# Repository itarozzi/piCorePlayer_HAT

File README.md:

# piCorePlayer RaspberryPi 3 HAT

A Raspberry Pi 3 HAT for my piCorePlayer device.

By Ivan Tarozzi
- itarozzi@gmail.com
- ivan.tarozzi@fablabromagna.org

> CAUTION!!!! Dont't use yet. The circuit is under test and the schema and PCB are probabily wrong due a wrong relay connection. I'll update the circuit as soon as possible

## Description
When I decided to use a RaspberryPi and the [piCorePlayer project](https://www.picoreplayer.org/) to stream my music library from NAS to HiFi I encountered the problem to have a proper PSU for the RaspberryPi, having the ability to shutdown the system in safe mode and using a HW button for a real ON/OFF.

This becasuse the RaspberryPi 3 lacks of a native way to halt and restart by buttons.

I found a solution in a forum (see credits) and I decided to create a prototype using handwired assembly.

But in the same days FablabRomagna (the FabLab where I play as maker here in Rimini-IT) organized a course about KiCad so I decided to give it a try. And here the result of my attempt to use KiCad for creating my HAT.

Instead of use dupont wires on the RaspberryPi 40-pin connector I created a HAT to connect the power module and at the same time use it for the DAC, the TFT display, the encoder and buttons for the front panel (piCorePlayer commands).

I used a lot of components I already owned, so I adapted the circuit to that things.

I creatd the PCB and using STEP file generated  by KiCad as reference, I created a case with FreeCAD.

## How it works

The power section use a latched relay to power the RaspberryPi throught the 40-pin GPIO connector, when a button is pressed. I changed the original circuit to use the same button to also poweroff the device.

So, in its initial state, the START/STOP button (replicated in PCB and front panel) drive the transistor Q1 to switch-on the relay and power on the RaspberryPi.

When the RaspberryPi is on and the START/STOP button  is pressed again, a high level is sent to GPIO_16 pin. A little daemon intercept this event and execute the safe power-off using linux commands.

When the RaspberryPi is halted, the GPIO_26 rise (using poweroff overlay) and this reset the relay via the Q2 transistor.
And additional safe button is used to activate Q2 if the software poweroff fails (hope ever used).

> there is a hypothetical race condition when the START/STOP button is pressed the first time, because when the relay switch its state, it rise the level on GPIO_16. But in real case, the Raspberry is booting so the shutdown daemon is not running until 10/12 seconds. I think it will works in this first version

## TODO

- may be a smd version
- DAC integration in the HAT

## License

- Hardware design is released under CERN-OHL-S v2 license
- Software is released under GPL3 License
- Documentation is released under CC BY-SA 3.0

## Credits

- [piCorePlayer project](https://www.picoreplayer.org/)
- [Seamus](https://raspberrypi.stackexchange.com/questions/142837/questions-on-dtoverlay-gpio-poweroff) for the power circuit
- [Maurizio Conti @ FablabRomagna](https://github.com/mconti) for forced me to try KiCad :)

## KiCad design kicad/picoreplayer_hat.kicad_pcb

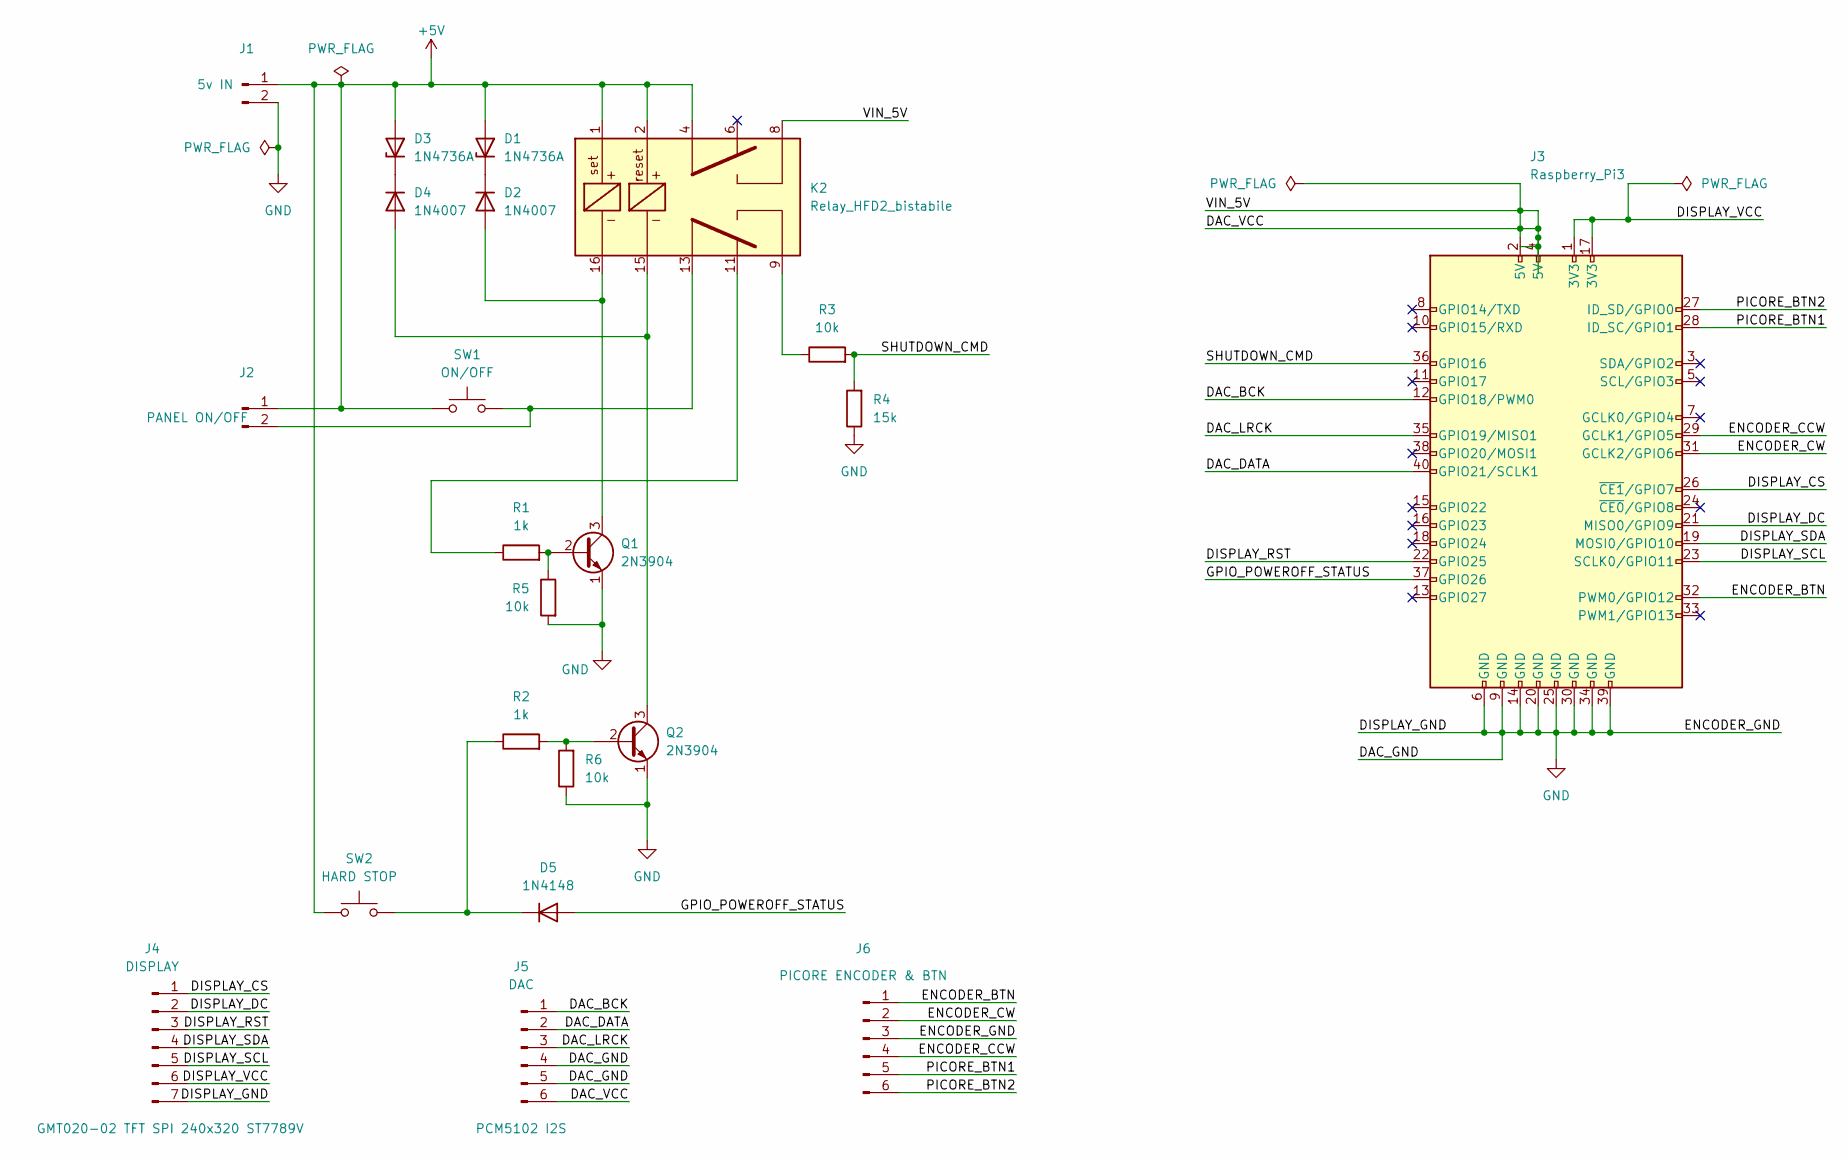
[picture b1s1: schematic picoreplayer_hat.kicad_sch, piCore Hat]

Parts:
D1, D3: 1N4736A; D_DO-41_SOD81_P7.62mm_Horizontal
D2, D4: 1N4007; D_DO-41_SOD81_P10.16mm_Horizontal
D5: 1N4148; D_DO-35_SOD27_P7.62mm_Horizontal
J1: 5v IN; JST_EH_B2B-EH-A_1x02_P2.50mm_Vertical
J2: PANEL ON/OFF; PinHeader_1x02_P2.54mm_Horizontal
J3: Raspberry_Pi3; PinSocket_2x20_P2.54mm_Vertical
J4: DISPLAY; PinHeader_1x07_P2.54mm_Horizontal
J5: DAC; PinHeader_1x06_P2.54mm_Horizontal
J6: PICORE ENCODER & BTN; PinHeader_1x06_P2.54mm_Horizontal
K2: Relay_HFD2_bistabile; Relay_HFD2-05ML2A_2 coils latching
Q1, Q2: 2N3904; TO-92_Inline
R1, R2: 1k; R_Axial_DIN0207_L6.3mm_D2.5mm_P7.62mm_Horizontal
R3, R5, R6: 10k; R_Axial_DIN0207_L6.3mm_D2.5mm_P7.62mm_Horizontal
R4: 15k; R_Axial_DIN0207_L6.3mm_D2.5mm_P7.62mm_Horizontal
SW1: ON/OFF; SW_PUSH_6mm_H4.3mm
SW2: HARD STOP; SW_PUSH_6mm_H4.3mm

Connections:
+5V: D1.2 (A), D3.2 (A), J1.1, J2.1, K2.1, K2.2, K2.4, SW1.1, SW2.1
/DAC_BCK: J3.12 (GPIO18/PWM0), J5.1
/DAC_DATA: J3.40 (GPIO21/SCLK1), J5.2
/DAC_LRCK: J3.35 (GPIO19/MISO1), J5.3
/DAC_VCC: J3.2 (5V), J3.4 (5V), J5.6, K2.8
/DISPLAY_CS: J3.26 (~CE1/GPIO7), J4.1
/DISPLAY_DC: J3.21 (MISO0/GPIO9), J4.2
/DISPLAY_RST: J3.22 (GPIO25), J4.3
/DISPLAY_SCL: J3.23 (SCLK0/GPIO11), J4.5
/DISPLAY_SDA: J3.19 (MOSI0/GPIO10), J4.4
/DISPLAY_VCC: J3.1 (3V3), J3.17 (3V3), J4.6
/ENCODER_BTN: J3.32 (PWM0/GPIO12), J6.1
/ENCODER_CCW: J3.29 (GCLK1/GPIO5), J6.4
/ENCODER_CW: J3.31 (GCLK2/GPIO6), J6.2
/GPIO_POWEROFF_STATUS: D5.2 (A), J3.37 (GPIO26)
/PICORE_BTN1: J3.28 (ID_SC/GPIO1), J6.5
/PICORE_BTN2: J3.27 (ID_SD/GPIO0), J6.6
/SHUTDOWN_CMD: J3.36 (GPIO16), R3.2, R4.2
GND: J1.2, J3.6 (GND), J3.9 (GND), J3.14 (GND), J3.20 (GND), J3.25 (GND), J3.30 (GND), J3.34 (GND), J3.39 (GND), J4.7, J5.4, J5.5, J6.3, Q1.1 (E), Q2.1 (E), R4.1, R5.2, R6.1
unnamed: D1.1 (K), D2.1 (K)
unnamed: D2.2 (A), K2.16, Q1.3 (C)
unnamed: D3.1 (K), D4.1 (K)
unnamed: D4.2 (A), K2.15, Q2.3 (C)
unnamed: D5.1 (K), R2.1, SW2.2
unnamed: J2.2, K2.13, SW1.2
unnamed: K2.9, R3.1
unnamed: K2.11, R1.1
unnamed: Q1.2 (B), R1.2, R5.1
unnamed: Q2.2 (B), R2.2, R6.2

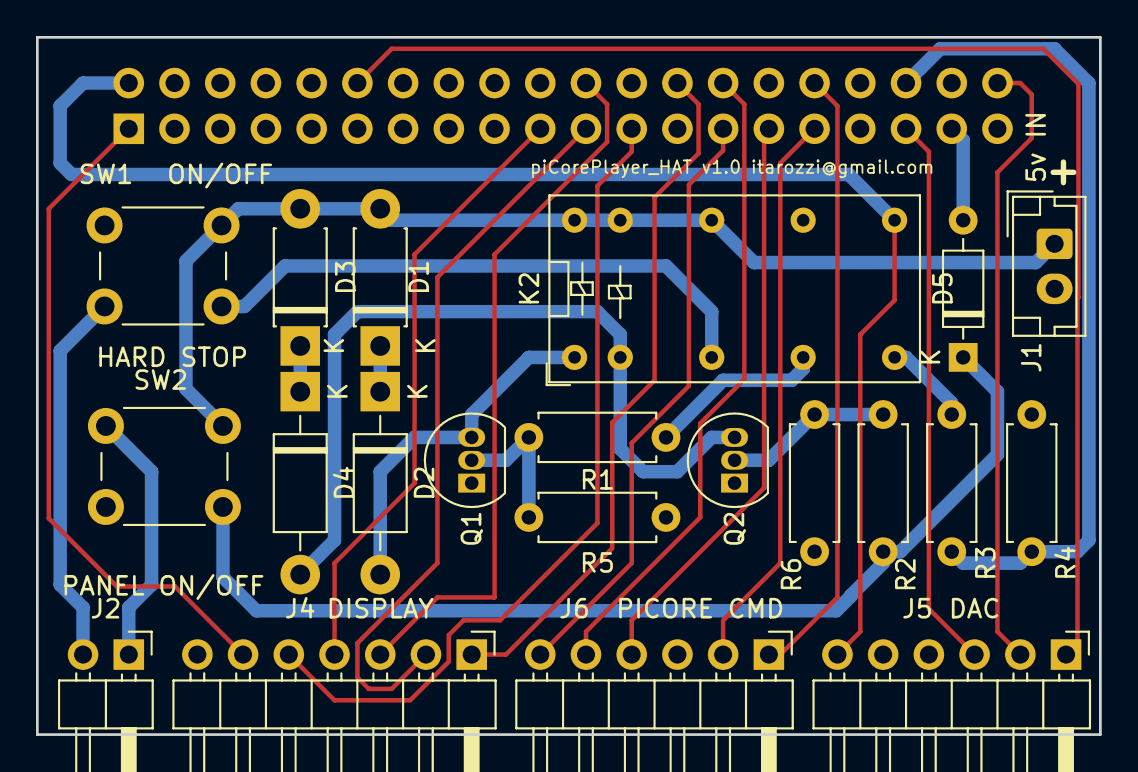
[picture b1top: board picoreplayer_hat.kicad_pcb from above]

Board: 2 copper layers, 59.1 x 38.7 mm, 22 parts (1 on the bottom side), 29 nets.

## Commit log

2024-02-12 increased PCB tracks for power section
2024-02-13 changed diode model to 1N4007 and added pulldown resistors to the transistor base
2024-02-13 update doc images
2024-02-14 changed symbols and footprint for 1N4007
2024-02-15 add CERN OHL license
